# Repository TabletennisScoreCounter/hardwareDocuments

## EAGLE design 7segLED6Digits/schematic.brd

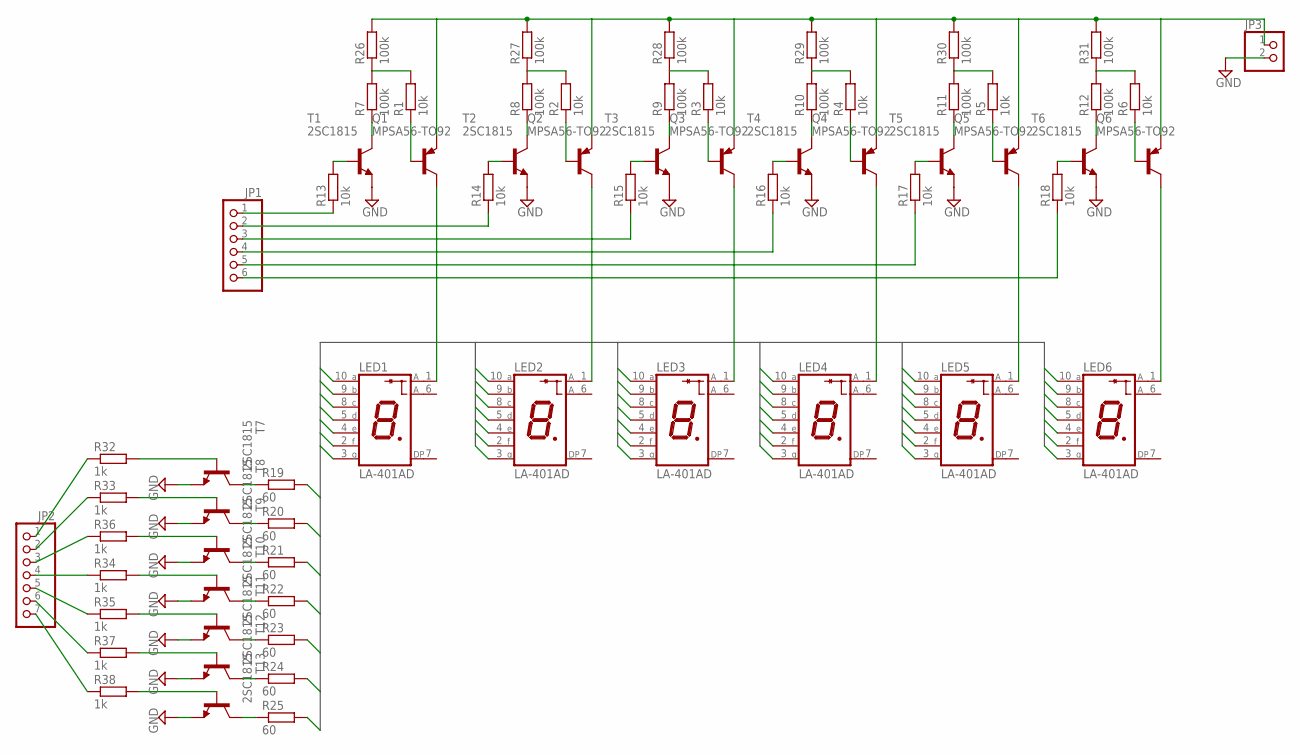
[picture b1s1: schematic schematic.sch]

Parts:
JP1: PINHD-1X6; 1X06
JP2: PINHD-1X7; 1X07
JP3: PINHD-1X2; 1X02
LED1, LED2, LED3, LED4, LED5, LED6: LA-401AD; LA-401
Q1, Q2, Q3, Q4, Q5, Q6: MPSA56-TO92; TO92-CBE
R1, R2, R3, R4, R5, R6, R13, R14, R15, R16, R17, R18: 10k; 0204/5
R7, R8, R9, R10, R11, R12, R26, R27, R28, R29, R30, R31: 100k; 0204/5
R19, R20, R21, R22, R23, R24, R25: 60; 0204/5
R32, R33, R34, R35, R36, R37, R38: 1k; 0204/5
T1, T2, T3, T4, T5, T6, T7, T8, T9, T10, T11, T12, T13: 2SC1815; TO92-ECB

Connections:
GND: JP3.2, T1.E, T2.E, T3.E, T4.E, T5.E, T6.E, T7.E, T8.E, T9.E, T10.E, T11.E, T12.E, T13.E
unnamed: R2.2, R8.2, R27.1
unnamed: Q2.B, R2.1
unnamed: Q4.B, R4.1
unnamed: R5.2, R11.2, R30.1
unnamed: Q5.B, R5.1
unnamed: Q6.B, R6.1
unnamed: JP3.1, Q1.E, Q2.E, Q3.E, Q4.E, Q5.E, Q6.E, R26.2, R27.2, R28.2, R29.2, R30.2, R31.2
unnamed: R13.2, T1.B
unnamed: Q1.B, R1.1
unnamed: R3.2, R9.2, R28.1
unnamed: R14.2, T2.B
unnamed: R15.2, T3.B
unnamed: Q3.B, R3.1
unnamed: R16.2, T4.B
unnamed: LED1.1 (A), Q1.C
unnamed: R17.2, T5.B
unnamed: LED2.1 (A), Q2.C
unnamed: LED3.1 (A), Q3.C
unnamed: R18.2, T6.B
unnamed: LED4.1 (A), Q4.C
unnamed: R1.2, R7.2, R26.1
unnamed: LED5.1 (A), Q5.C
unnamed: LED6.1 (A), Q6.C
unnamed: R4.2, R10.2, R29.1
unnamed: R6.2, R12.2, R31.1
unnamed: R19.1, T7.C
unnamed: R25.1, T13.C
unnamed: R24.1, T12.C
unnamed: R23.1, T11.C
unnamed: R22.1, T10.C
unnamed: R21.1, T9.C
unnamed: R7.1, T1.C
unnamed: R8.1, T2.C
unnamed: R9.1, T3.C
unnamed: R12.1, T6.C
unnamed: R11.1, T5.C
unnamed: R10.1, T4.C
unnamed: R20.1, T8.C
unnamed: R32.2, T7.B
unnamed: R33.2, T8.B
unnamed: R36.2, T9.B
unnamed: R34.2, T10.B
unnamed: R35.2, T11.B
unnamed: R37.2, T12.B
unnamed: R38.2, T13.B
unnamed: JP2.1, R32.1
unnamed: JP2.2, R33.1
unnamed: JP2.3, R36.1
unnamed: JP2.4, R34.1
unnamed: JP2.5, R35.1
unnamed: JP2.6, R37.1
unnamed: JP2.7, R38.1
unnamed: JP1.1, R13.1
unnamed: JP1.2, R14.1
unnamed: JP1.3, R15.1
unnamed: JP1.4, R16.1
unnamed: JP1.5, R17.1
unnamed: JP1.6, R18.1
SEGMENT1: LED1.3 (G), LED2.3 (G), LED3.3 (G), LED4.3 (G), LED5.3 (G), LED6.3 (G), R25.2
SEGMENT2: LED1.2 (F), LED2.2 (F), LED3.2 (F), LED4.2 (F), LED5.2 (F), LED6.2 (F), R24.2
SEGMENT3: LED1.4 (E), LED2.4 (E), LED3.4 (E), LED4.4 (E), LED5.4 (E), LED6.4 (E), R23.2
SEGMENT4: LED1.5 (D), LED2.5 (D), LED3.5 (D), LED4.5 (D), LED5.5 (D), LED6.5 (D), R22.2
SEGMENT5: LED1.8 (C), LED2.8 (C), LED3.8 (C), LED4.8 (C), LED5.8 (C), LED6.8 (C), R21.2
SEGMENT6: LED1.9 (B), LED2.9 (B), LED3.9 (B), LED4.9 (B), LED5.9 (B), LED6.9 (B), R20.2
SEGMENT7: LED1.10 (A), LED2.10 (A), LED3.10 (A), LED4.10 (A), LED5.10 (A), LED6.10 (A), R19.2

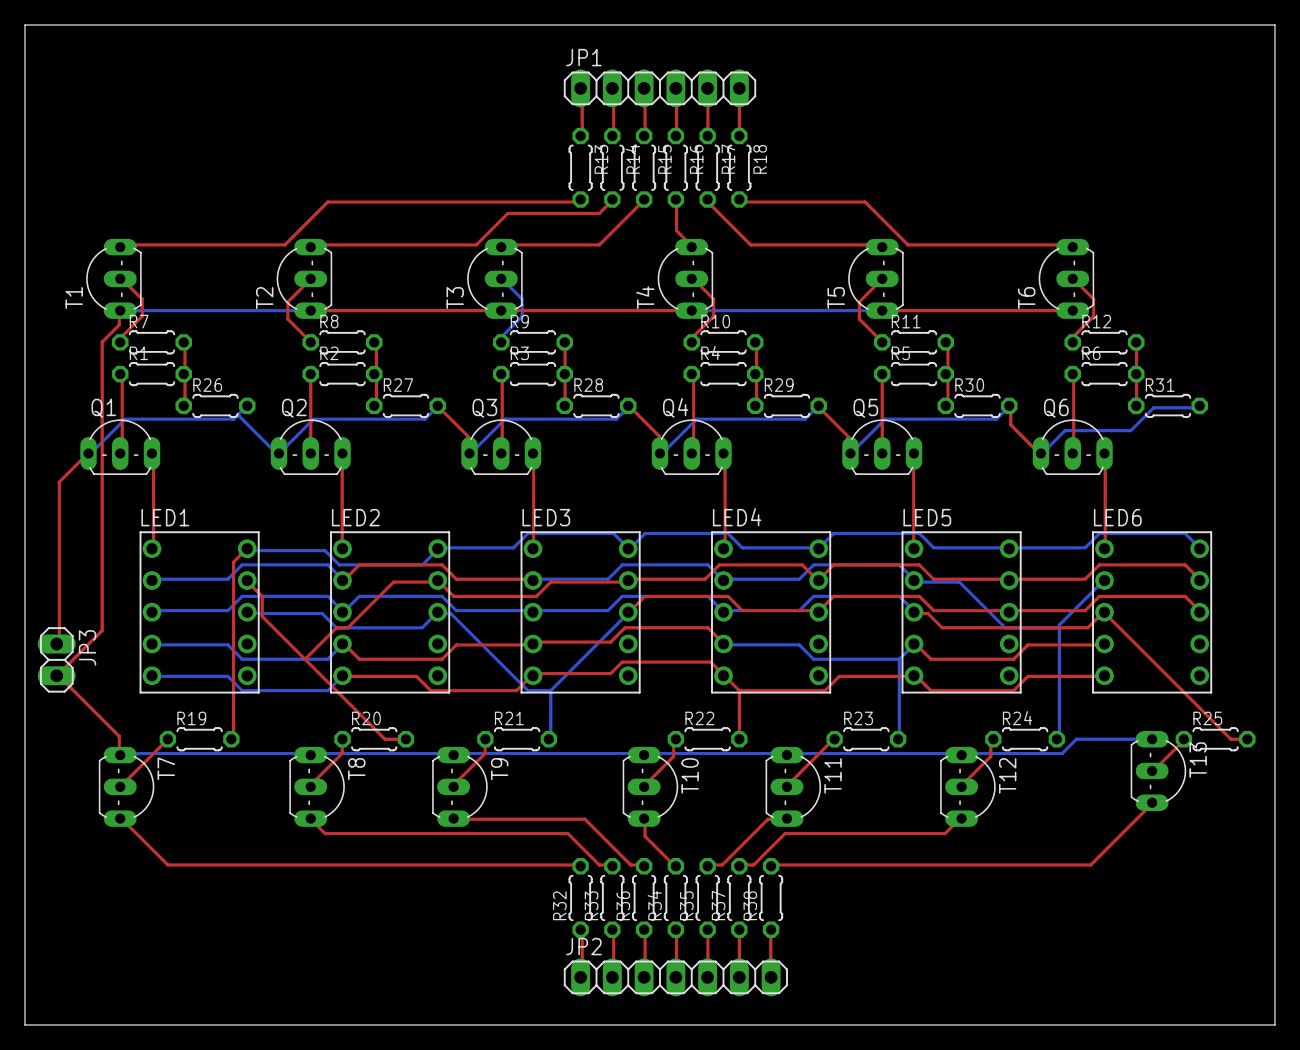
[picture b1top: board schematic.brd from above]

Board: 2 copper layers, 100.0 x 80.0 mm, 66 parts (0 on the bottom side), 66 nets.

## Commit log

2016-12-06 スケマ修正, ボード図追加
2016-12-07 PNPのベース電圧分圧用抵抗追加 ボード図追加
2016-12-28 ユニバーサル回路追加
2017-05-30 ピン接続を追加
